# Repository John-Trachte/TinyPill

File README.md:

# TinyPill
Design of a minimal STM32 development board based on the WEMOS S2 Mini form factor featuring the microprossesor from the STM32 Blue Pill.

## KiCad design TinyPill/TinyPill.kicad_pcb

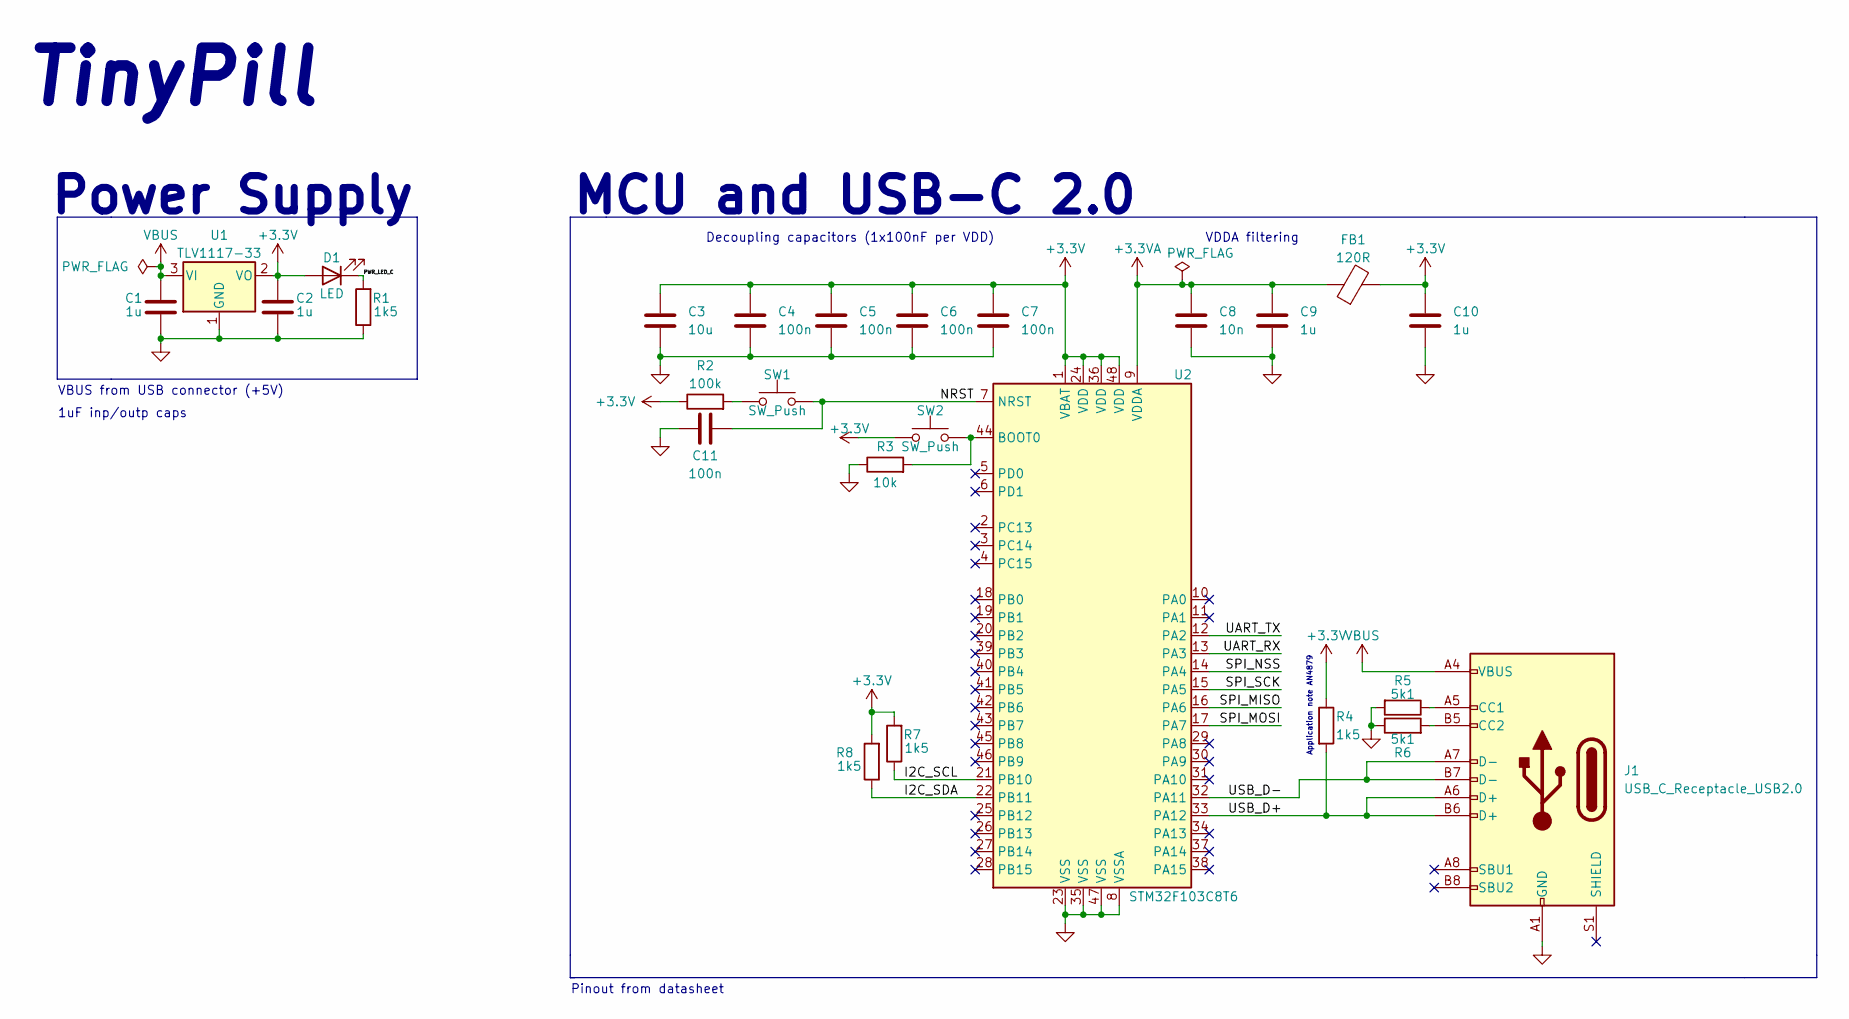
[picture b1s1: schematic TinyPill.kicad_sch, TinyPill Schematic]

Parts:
C1, C2, C9, C10: 1u; C_0603_1608Metric
C3: 10u; C_0603_1608Metric
C4, C5, C6, C7, C11: 100n; C_0402_1005Metric
C8: 10n; C_0402_1005Metric
D1: LED; LED_0603_1608Metric
FB1: 120R; L_0603_1608Metric
J1: USB_C_Receptacle_USB2.0; USB_C_Receptacle_GCT_USB4085
R1, R4, R7, R8: 1k5; R_0402_1005Metric
R2: 100k; R_0402_1005Metric
R3: 10k; R_0402_1005Metric
R5, R6: 5k1; R_0603_1608Metric
SW1: SW_Push; SW_Push_SPST_NO_Alps_SKRK
SW2: SW_Push; SW_DIP_SPSTx01_Slide_Omron_A6S-110x_W8.9mm_P2.54mm
U1: TLV1117-33; SOT-223-3_TabPin2
U2: STM32F103C8T6; LQFP-48_7x7mm_P0.5mm

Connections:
+3.3VA: C8.1, C9.1, FB1.1, U2.9 (VDDA)
+3V3: C2.1, C3.1, C4.1, C5.1, C6.1, C7.1, C10.1, D1.2 (A), FB1.2, R2.1, R4.1, R7.2, R8.2, SW2.1, U1.2 (VO), U2.1 (VBAT), U2.24 (VDD), U2.36 (VDD), U2.48 (VDD)
/I2C_SCL: R7.1, U2.21 (PB10)
/I2C_SDA: R8.1, U2.22 (PB11)
/NRST: C11.1, SW1.2, U2.7 (NRST)
/PWR_LED_C: D1.1 (K), R1.2
/SPI_MISO: U2.16 (PA6)
/SPI_MOSI: U2.17 (PA7)
/SPI_NSS: U2.14 (PA4)
/SPI_SCK: U2.15 (PA5)
/UART_RX: U2.13 (PA3)
/UART_TX: U2.12 (PA2)
/USB_D+: J1.A6 (D+), J1.B6 (D+), R4.2, U2.33 (PA12)
/USB_D-: J1.A7 (D-), J1.B7 (D-), U2.32 (PA11)
GND: C1.2, C2.2, C3.2, C4.2, C5.2, C6.2, C7.2, C8.2, C9.2, C10.2, C11.2, J1.A1 (GND), J1.A12 (GND), J1.B1 (GND), J1.B12 (GND), R1.1, R3.1, R5.2, R6.1, U1.1 (GND), U2.8 (VSSA), U2.23 (VSS), U2.35 (VSS), U2.47 (VSS)
unnamed: J1.A5 (CC1), R5.1
unnamed: J1.B5 (CC2), R6.2
unnamed: R2.2, SW1.1
unnamed: R3.2, SW2.2, U2.44 (BOOT0)
VBUS: C1.1, J1.A4 (VBUS), J1.A9 (VBUS), J1.B4 (VBUS), J1.B9 (VBUS), U1.3 (VI)

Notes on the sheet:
Application note AN4879
VDDA filtering
Decoupling capacitors (1x100nF per VDD)
TinyPill
MCU and USB-C 2.0
Power Supply
1uF inp/outp caps
Pinout from datasheet
VBUS from USB connector (+5V)

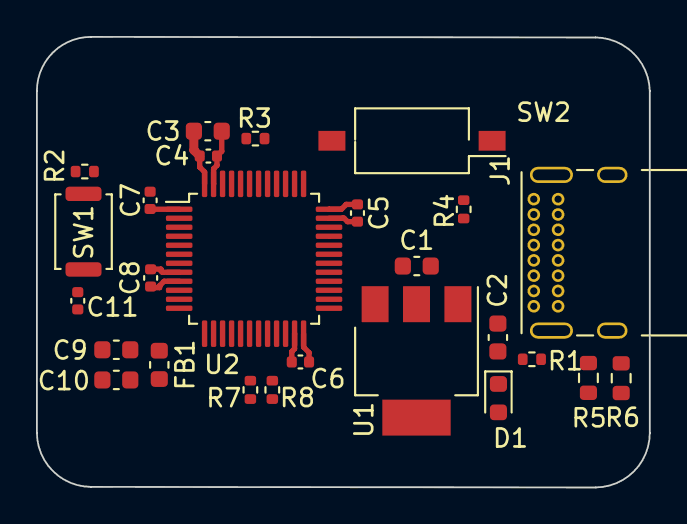
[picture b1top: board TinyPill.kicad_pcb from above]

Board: 2 copper layers, 34.1 x 25.0 mm, 26 parts (0 on the bottom side), 14 nets.

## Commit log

2023-11-15 Update README to reflect name change
2023-11-20 Create KiCad project, first pass of schematic
2023-11-21 Finish GPIO selection
2023-11-24 Annotations, footprint assignment
2023-11-24 Update form-factor
2023-11-24 Initial layout, begin routing
2023-11-28 Add gitignore
2023-11-28 Change USB C port to USB B Micro to support smaller board footprint
